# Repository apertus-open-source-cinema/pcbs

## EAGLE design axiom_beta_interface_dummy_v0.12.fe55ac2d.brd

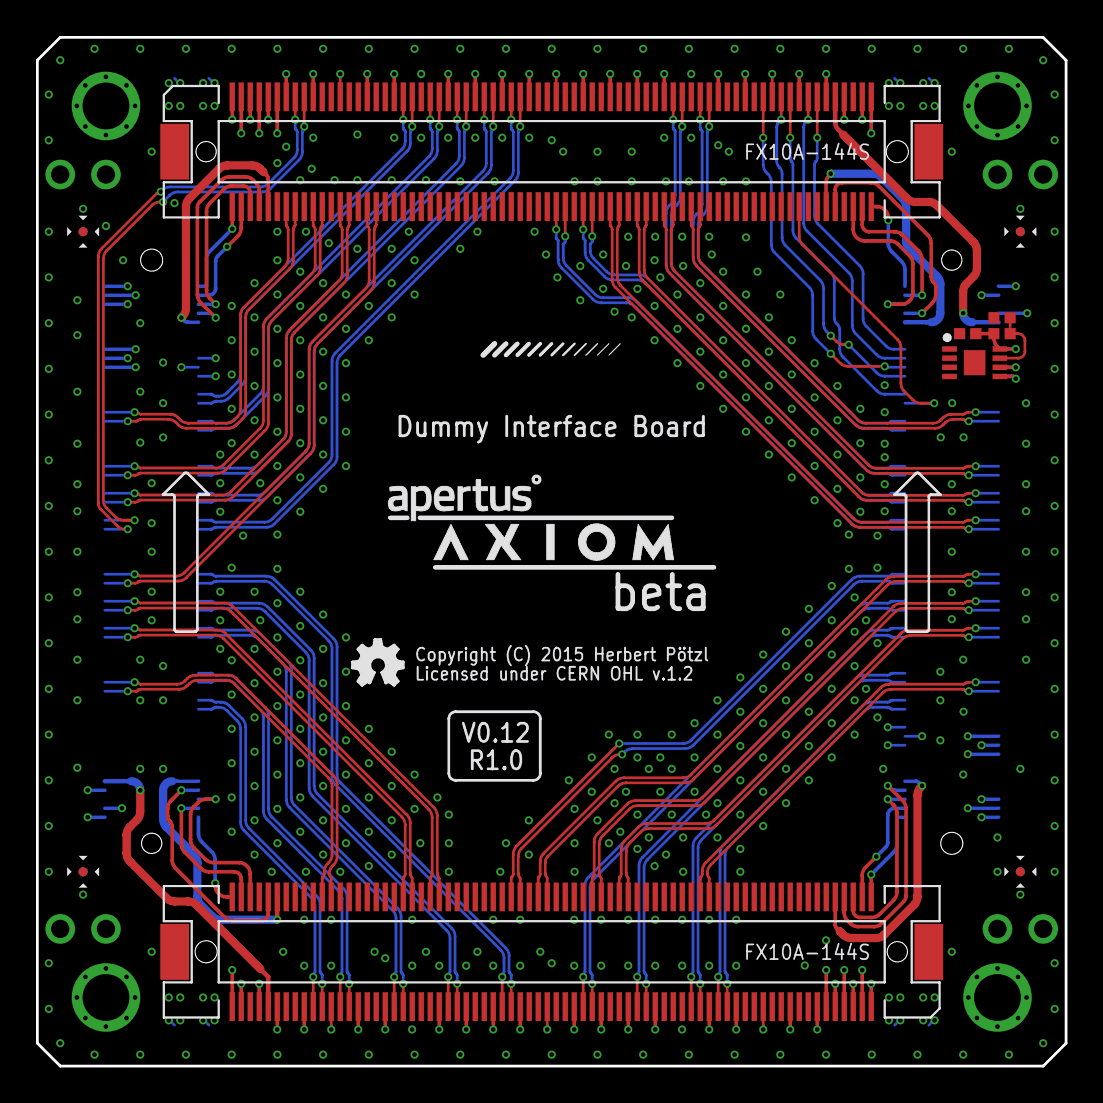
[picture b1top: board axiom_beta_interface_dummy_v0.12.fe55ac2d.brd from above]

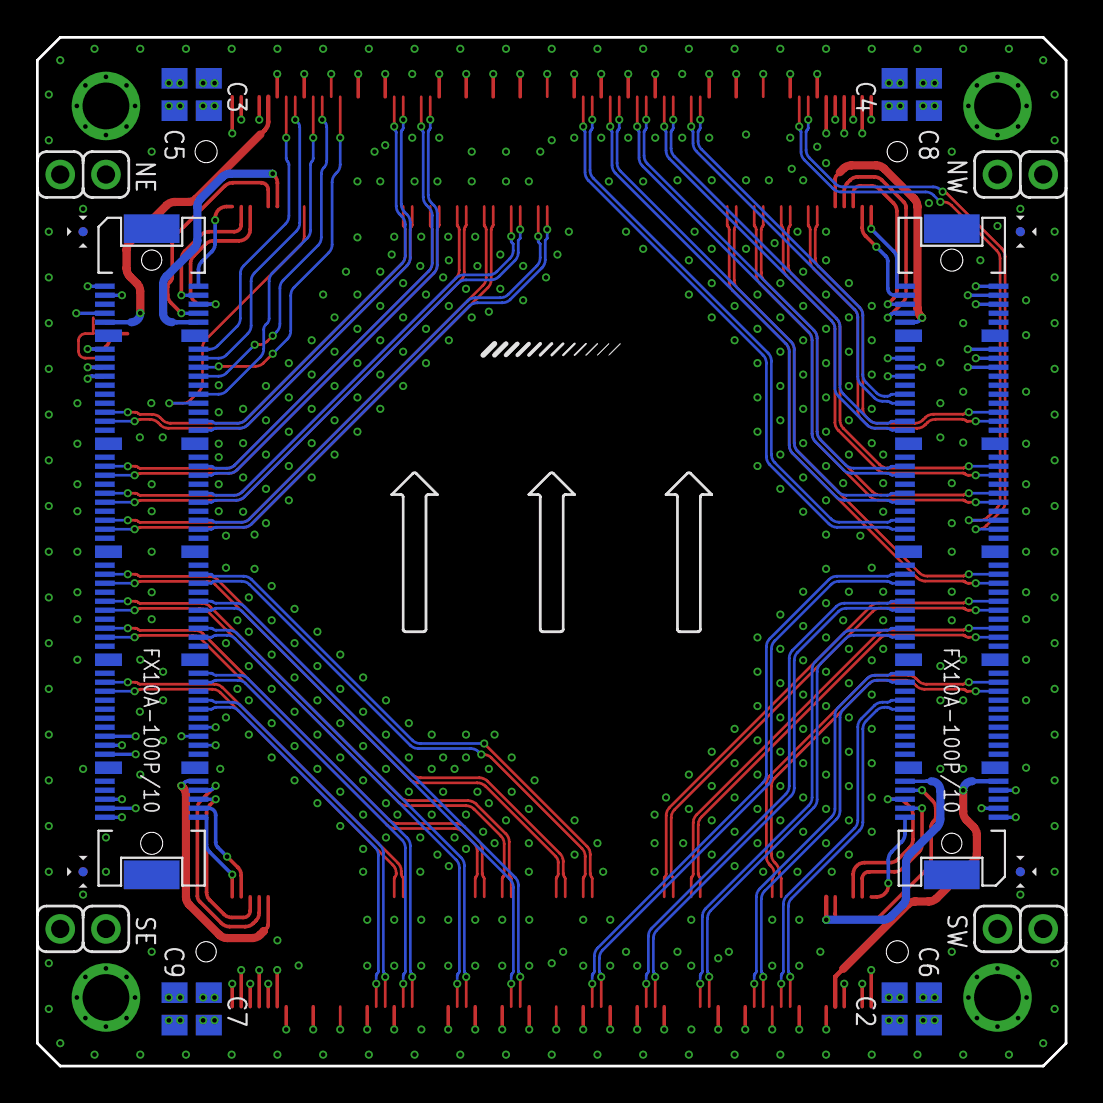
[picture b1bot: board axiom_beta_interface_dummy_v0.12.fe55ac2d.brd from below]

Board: 4 copper layers, 57.1 x 57.1 mm, 25 parts (14 on the bottom side), 135 nets.

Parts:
C1: 0402-B
C2, C3, C4, C5, C6, C7, C8, C9: 0805-B
LOGO1: OSHW_LOGO_FILLX0100-NT; OSHW_FILLX100_NOTEXT
NE: 1X02
NW: 1X02
PARALLELLA: PARALLELLA-FRAME
R1, R2: 0402-B
SE: 1X02
SW: 1X02
U1: BR24G04NUX; DFN200X300X100-9N
U$1: µZ-FRAME
U$2: APERTUS_LOGO334X100; APERTUS_LOGO_334X100
U$3: AXIOM_LOGO525X80; AXIOM_LOGO_525X80
X-EAST: FX10-100/10P; FX10A-100P/10
X-NORTH: FX10-144S; FX10A-144S
X-SOUTH: FX10-144S; FX10A-144S
X-WEST: FX10-100/10P; FX10A-100P/10

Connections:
CLK_IN: X-EAST.24, X-NORTH.128
E_I2C_V: C1.1, R1.1, U1.8, X-EAST.11
E_SCL: U1.6, X-EAST.15
E_SDA: U1.5, X-EAST.17
E_VE: C9.1, SE.2
FRAME_REQ: X-EAST.14, X-NORTH.129
GND: C1.2, C2.2, C3.2, C4.2, C5.2, C6.2, C7.2, C8.2, C9.2, R2.2, U1.1, U1.2, U1.3, U1.4, U1.EP, X-EAST.5, X-EAST.20, X-EAST.23, X-EAST.26, X-EAST.29, X-EAST.31, X-EAST.32, X-EAST.37, X-EAST.38, X-EAST.43, X-EAST.44, X-EAST.49, X-EAST.50, X-EAST.51, X-EAST.52, X-EAST.57, X-EAST.58, X-EAST.63, X-EAST.64, X-EAST.69, X-EAST.70, X-EAST.71, X-EAST.76, X-EAST.77, X-EAST.82, X-EAST.G1, X-EAST.G2, X-EAST.G3, X-EAST.G4, X-EAST.G5, X-EAST.G6, X-EAST.G7, X-EAST.G8, X-EAST.G9, X-EAST.G10, X-NORTH.12, X-NORTH.18, X-NORTH.24, X-NORTH.30, X-NORTH.36, X-NORTH.42, X-NORTH.43, X-NORTH.48, X-NORTH.54, X-NORTH.60, X-NORTH.66, X-NORTH.72, X-NORTH.78, X-NORTH.84, X-NORTH.90, X-NORTH.96, X-NORTH.102, X-NORTH.103, X-NORTH.108, X-NORTH.114, X-NORTH.120, X-NORTH.126, X-NORTH.132, X-NORTH.138, X-NORTH.139, X-SOUTH.12, X-SOUTH.18, X-SOUTH.24, X-SOUTH.30, X-SOUTH.36, X-SOUTH.42, X-SOUTH.43, X-SOUTH.48, X-SOUTH.54, X-SOUTH.60, X-SOUTH.66, X-SOUTH.72, X-SOUTH.78, X-SOUTH.84, X-SOUTH.90, X-SOUTH.96, X-SOUTH.102, X-SOUTH.103, X-SOUTH.108, X-SOUTH.114, X-SOUTH.120, X-SOUTH.126, X-SOUTH.132, X-SOUTH.138, X-SOUTH.139, X-WEST.5, X-WEST.20, X-WEST.23, X-WEST.26, X-WEST.29, X-WEST.31, X-WEST.32, X-WEST.37, X-WEST.38, X-WEST.43, X-WEST.44, X-WEST.49, X-WEST.50, X-WEST.51, X-WEST.52, X-WEST.57, X-WEST.58, X-WEST.63, X-WEST.64, X-WEST.69, X-WEST.70, X-WEST.71, X-WEST.76, X-WEST.77, X-WEST.82, X-WEST.G1, X-WEST.G2, X-WEST.G3, X-WEST.G4, X-WEST.G5, X-WEST.G6, X-WEST.G7, X-WEST.G8, X-WEST.G9, X-WEST.G10
LVDS_CLK_N: X-NORTH.14, X-WEST.75
LVDS_CLK_P: X-NORTH.16, X-WEST.73
unnamed: R1.2, R2.1, U1.7
N_CHK_EN: X-NORTH.8, X-WEST.94
N_CHK_V: X-NORTH.10, X-WEST.92
N_I2C_EN: X-EAST.7, X-NORTH.137
N_I2C_V: X-EAST.9, X-NORTH.135
N_SCK: X-EAST.2, X-NORTH.144
N_SCL: X-EAST.1, X-NORTH.143
N_SDA: X-EAST.3, X-NORTH.141
N_SDI: X-EAST.6, X-NORTH.140
N_SDO: X-EAST.4, X-NORTH.142
N_SPI_EN: X-EAST.8, X-NORTH.136
N_SPI_V: X-EAST.10, X-NORTH.134
N_VE: C5.1, NE.2, X-NORTH.109, X-NORTH.115, X-NORTH.127, X-NORTH.133
N_VE_CV: X-NORTH.6, X-WEST.96
N_VE_OV: X-NORTH.5, X-WEST.95
N_VE_RS: X-NORTH.121, X-WEST.88
N_VE_UV: X-NORTH.11, X-WEST.85
N_VN: C3.1, NE.1, X-NORTH.49, X-NORTH.55, X-NORTH.61, X-NORTH.67, X-NORTH.79, X-NORTH.85, X-NORTH.91, X-NORTH.97
N_VN_CV: X-NORTH.4, X-WEST.98
N_VN_OV: X-NORTH.3, X-WEST.97
N_VN_RS: X-NORTH.73, X-WEST.86
N_VN_UV: X-NORTH.9, X-WEST.87
N_VW: C4.1, NW.1, X-NORTH.13, X-NORTH.19, X-NORTH.31, X-NORTH.37
N_VW_CV: X-NORTH.2, X-WEST.100
N_VW_OV: X-NORTH.1, X-WEST.99
N_VW_RS: X-NORTH.25, X-WEST.84
N_VW_UV: X-NORTH.7, X-WEST.89
OUT1_N: X-SOUTH.119, X-WEST.28
OUT1_P: X-SOUTH.117, X-WEST.30
OUT3_N: X-SOUTH.124, X-WEST.25
OUT3_P: X-SOUTH.122, X-WEST.27
OUT5_N: X-SOUTH.107, X-WEST.34
OUT5_P: X-SOUTH.105, X-WEST.36
OUT7_N: X-SOUTH.106, X-WEST.33
OUT7_P: X-SOUTH.104, X-WEST.35
OUT9_N: X-SOUTH.95, X-WEST.40
OUT9_P: X-SOUTH.93, X-WEST.42
OUT11_N: X-SOUTH.100, X-WEST.39
OUT11_P: X-SOUTH.98, X-WEST.41
OUT13_N: X-SOUTH.83, X-WEST.46
OUT13_P: X-SOUTH.81, X-WEST.48
OUT15_N: X-EAST.54, X-SOUTH.82
OUT15_P: X-EAST.56, X-SOUTH.80
OUT17_N: X-EAST.53, X-SOUTH.76
OUT17_P: X-EAST.55, X-SOUTH.74
OUT19_N: X-EAST.60, X-SOUTH.65
OUT19_P: X-EAST.62, X-SOUTH.63
OUT21_N: X-EAST.59, X-SOUTH.64
OUT21_P: X-EAST.61, X-SOUTH.62
OUT23_N: X-EAST.66, X-SOUTH.53
OUT23_P: X-EAST.68, X-SOUTH.51
OUT25_N: X-EAST.65, X-SOUTH.58
OUT25_P: X-EAST.67, X-SOUTH.56
OUT27_N: X-EAST.73, X-SOUTH.40
OUT27_P: X-EAST.75, X-SOUTH.38
OUT29_N: X-EAST.72, X-SOUTH.41
OUT29_P: X-EAST.74, X-SOUTH.39
OUT31_N: X-EAST.78, X-SOUTH.35
OUT31_P: X-EAST.80, X-SOUTH.33
OUT33_N: X-NORTH.20, X-WEST.67
OUT33_P: X-NORTH.22, X-WEST.65
OUT35_N: X-NORTH.26, X-WEST.61
OUT35_P: X-NORTH.28, X-WEST.59
OUT37_N: X-NORTH.32, X-WEST.47
OUT37_P: X-NORTH.34, X-WEST.45
OUT39_N: X-NORTH.39, X-WEST.80
OUT39_P: X-NORTH.41, X-WEST.78
OUT41_N: X-NORTH.45, X-WEST.74
OUT41_P: X-NORTH.47, X-WEST.72
OUT43_N: X-NORTH.51, X-WEST.68
OUT43_P: X-NORTH.53, X-WEST.66
OUT45_N: X-NORTH.57, X-WEST.62
OUT45_P: X-NORTH.59, X-WEST.60
OUT47_N: X-NORTH.63, X-WEST.56
OUT47_P: X-NORTH.65, X-WEST.54
OUT49_N: X-EAST.48, X-NORTH.74
OUT49_P: X-EAST.46, X-NORTH.76
OUT51_N: X-EAST.42, X-NORTH.80
OUT51_P: X-EAST.40, X-NORTH.82
OUT53_N: X-EAST.47, X-NORTH.86
OUT53_P: X-EAST.45, X-NORTH.88
OUT55_N: X-EAST.41, X-NORTH.92
OUT55_P: X-EAST.39, X-NORTH.94
OUT57_N: X-EAST.35, X-NORTH.98
OUT57_P: X-EAST.33, X-NORTH.100
OUT59_N: X-EAST.27, X-NORTH.104
OUT59_P: X-EAST.25, X-NORTH.106
OUT61_N: X-EAST.36, X-NORTH.99
OUT61_P: X-EAST.34, X-NORTH.101
OUT63_N: X-EAST.30, X-NORTH.105
OUT63_P: X-EAST.28, X-NORTH.107
OUTCLK_N: X-NORTH.15, X-WEST.53
OUTCLK_P: X-NORTH.17, X-WEST.55
OUTCTR_N: X-SOUTH.125, X-WEST.22
OUTCTR_P: X-SOUTH.123, X-WEST.24
SYS_RES_N: X-EAST.22, X-NORTH.125
S_CHK_EN: X-EAST.94, X-SOUTH.8
S_CHK_V: X-EAST.92, X-SOUTH.10
S_I2C_EN: X-SOUTH.137, X-WEST.7
S_I2C_V: X-SOUTH.135, X-WEST.9
S_SCK: X-SOUTH.144, X-WEST.2
S_SCL: X-SOUTH.143, X-WEST.1
S_SDA: X-SOUTH.141, X-WEST.3
S_SDI: X-SOUTH.140, X-WEST.6
S_SDO: X-SOUTH.142, X-WEST.4
S_SPI_EN: X-SOUTH.136, X-WEST.8
S_SPI_V: X-SOUTH.134, X-WEST.10
S_VE: C7.1, SE.1, X-SOUTH.13, X-SOUTH.19, X-SOUTH.31, X-SOUTH.37
S_VE_CV: X-EAST.100, X-SOUTH.2
S_VE_OV: X-EAST.99, X-SOUTH.1
S_VE_RS: X-EAST.84, X-SOUTH.25
S_VE_UV: X-EAST.89, X-SOUTH.7
S_VS: C6.1, SW.1, X-SOUTH.49, X-SOUTH.55, X-SOUTH.61, X-SOUTH.67, X-SOUTH.79, X-SOUTH.85, X-SOUTH.91, X-SOUTH.97
S_VS_CV: X-EAST.98, X-SOUTH.4
S_VS_OV: X-EAST.97, X-SOUTH.3
S_VS_RS: X-EAST.86, X-SOUTH.73
S_VS_UV: X-EAST.87, X-SOUTH.9
S_VW: C2.1, SW.2, X-SOUTH.109, X-SOUTH.115, X-SOUTH.127, X-SOUTH.133
S_VW_CV: X-EAST.96, X-SOUTH.6
S_VW_OV: X-EAST.95, X-SOUTH.5
S_VW_RS: X-EAST.88, X-SOUTH.121
S_VW_UV: X-EAST.85, X-SOUTH.11
TDIG1: X-EAST.18, X-NORTH.123
T_EXP1: X-EAST.12, X-NORTH.131
T_EXP2: X-EAST.16, X-NORTH.119
W_VW: C8.1, NW.2

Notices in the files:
axiom_beta_interface_dummy_v0.12.fe55ac2d.brd:
Copyright (C) 2015 Herbert Pötzl
Licensed under CERN OHL v.1.2
